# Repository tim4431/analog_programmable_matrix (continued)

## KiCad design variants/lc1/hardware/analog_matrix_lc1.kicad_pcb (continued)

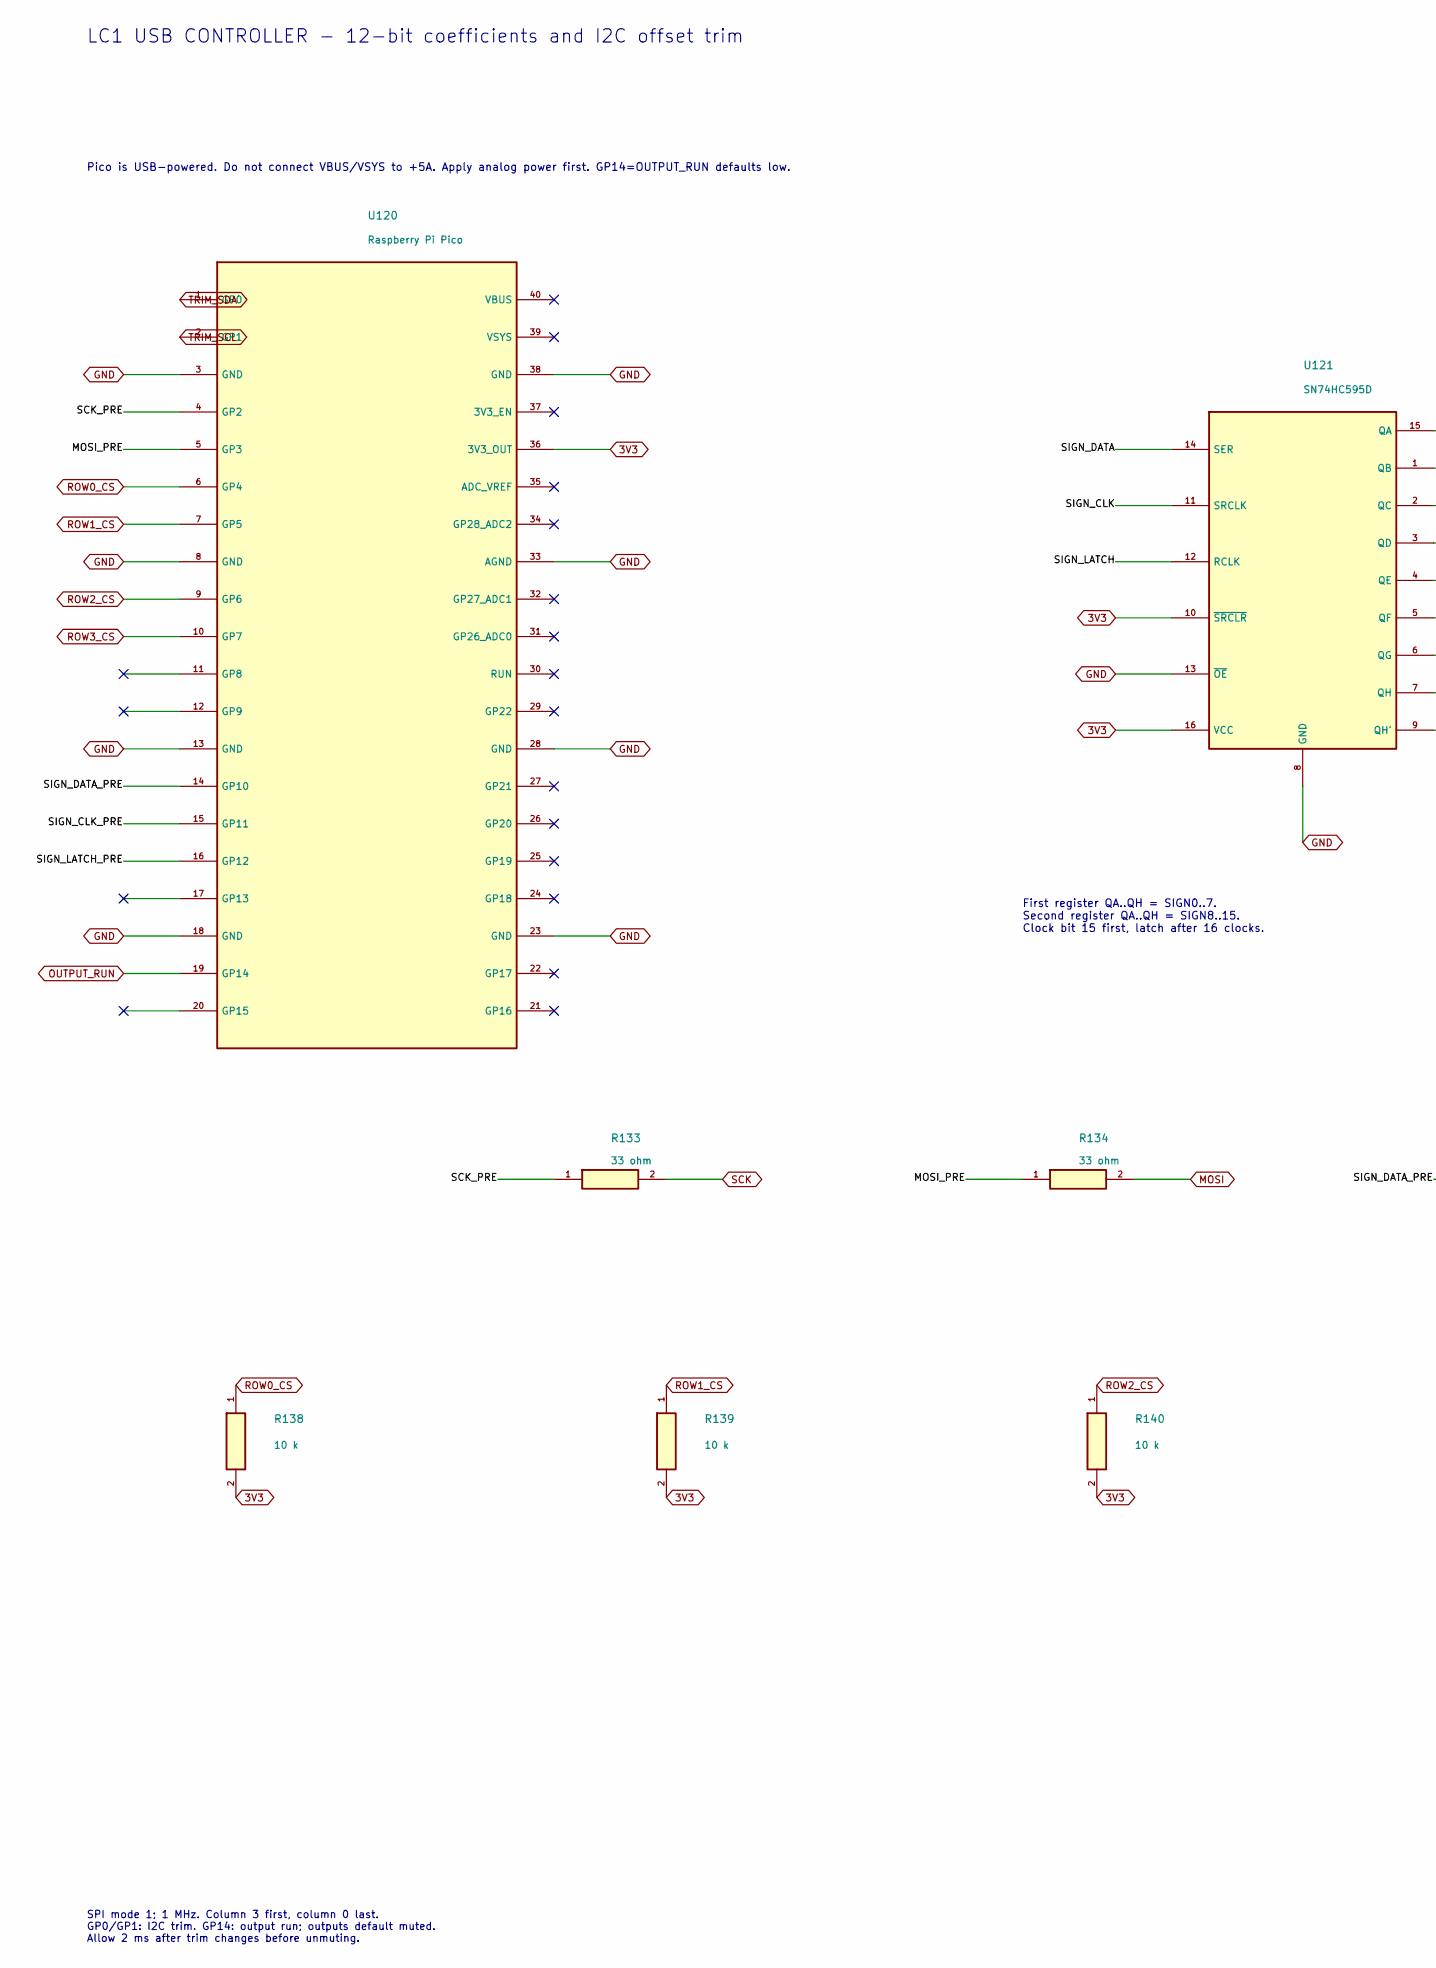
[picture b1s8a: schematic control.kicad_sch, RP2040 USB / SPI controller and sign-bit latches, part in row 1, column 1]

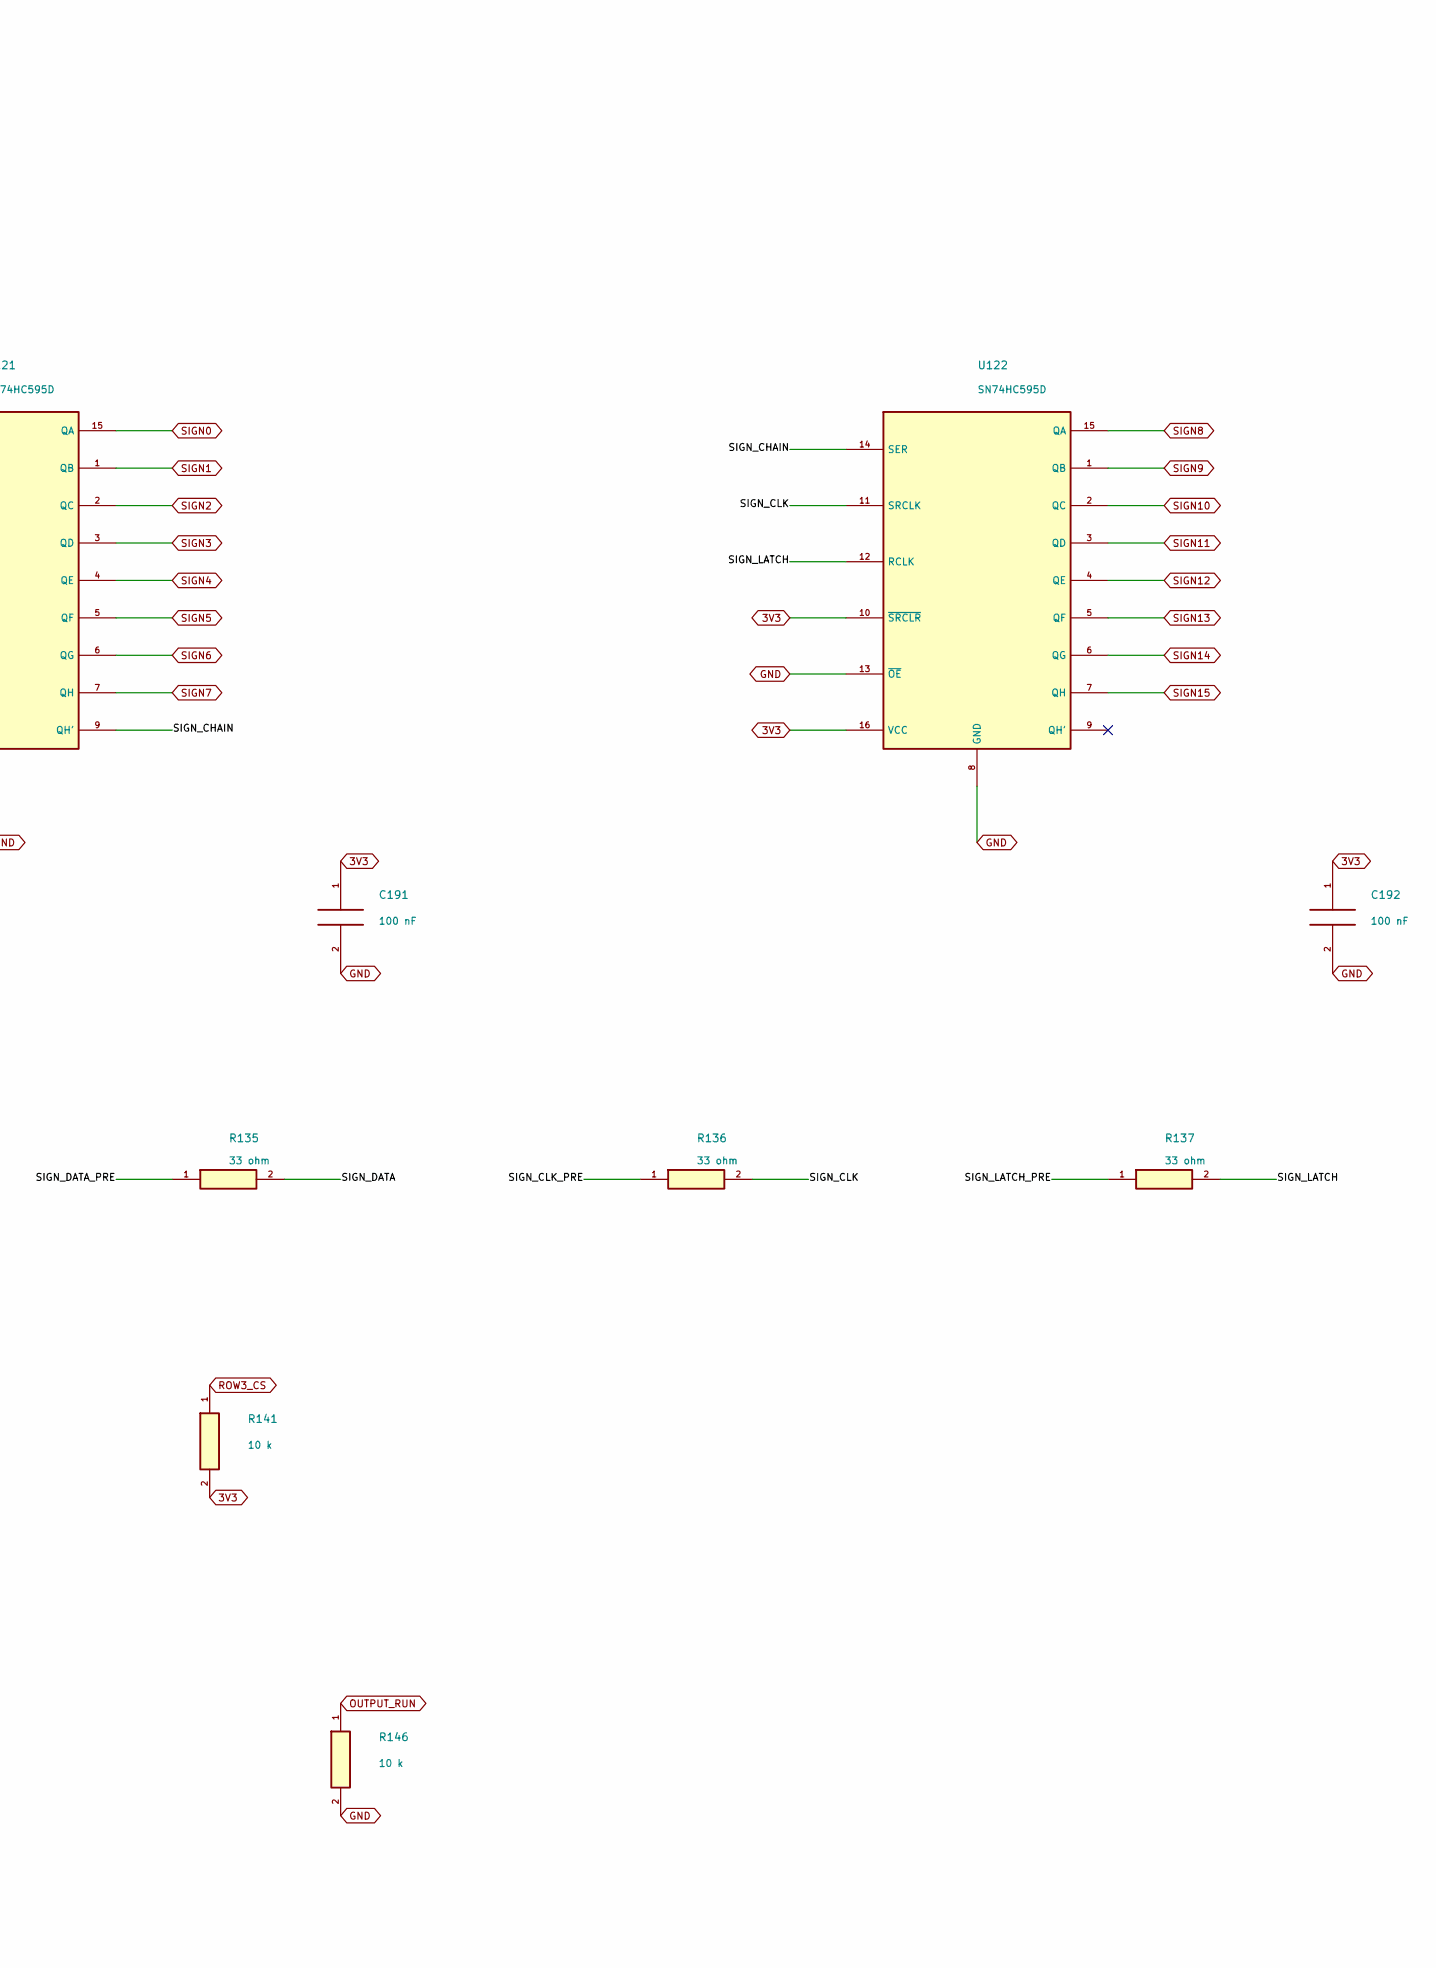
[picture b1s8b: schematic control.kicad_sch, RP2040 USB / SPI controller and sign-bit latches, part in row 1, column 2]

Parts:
C191, C192: 100 nF; C_0603_1608Metric; Rating 25V X7R minimum; effective C after bias
R133, R134, R135, R136, R137: 33 ohm; R_0603_1608Metric; Rating 0.1%, <=25ppm/C; 0.1W minimum
R138, R139, R140, R141, R146: 10 k; R_0603_1608Metric; Rating 0.1%, <=25ppm/C; 0.1W minimum
U120: Raspberry Pi Pico; Pico_2x20_Socket_17.78mm
U121, U122: SN74HC595D; SOIC-16_3.9x9.9mm_P1.27mm

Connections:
3V3: C191.1, C192.1, R138.2, R139.2, R140.2, R141.2, U120.36 (3V3_OUT), U121.10 (~SRCLR), U121.16 (VCC), U122.10 (~SRCLR), U122.16 (VCC); also elsewhere on the board
/Control/MOSI_PRE: R134.1, U120.5 (GP3)
/Control/SCK_PRE: R133.1, U120.4 (GP2)
/Control/SIGN_CHAIN: U121.9 (QH'), U122.14 (SER)
/Control/SIGN_CLK: R136.2, U121.11 (SRCLK), U122.11 (SRCLK)
/Control/SIGN_CLK_PRE: R136.1, U120.15 (GP11)
/Control/SIGN_DATA: R135.2, U121.14 (SER)
/Control/SIGN_DATA_PRE: R135.1, U120.14 (GP10)
/Control/SIGN_LATCH: R137.2, U121.12 (RCLK), U122.12 (RCLK)
/Control/SIGN_LATCH_PRE: R137.1, U120.16 (GP12)
GND: C191.2, C192.2, R146.2, U120.3 (GND), U120.8 (GND), U120.13 (GND), U120.18 (GND), U120.23 (GND), U120.28 (GND), U120.33 (AGND), U120.38 (GND), U121.8 (GND), U121.13 (~OE), U122.8 (GND), U122.13 (~OE); also elsewhere on the board
MOSI: R134.2; also elsewhere on the board
OUTPUT_RUN: R146.1, U120.19 (GP14); also elsewhere on the board
ROW0_CS: R138.1, U120.6 (GP4); also elsewhere on the board
ROW1_CS: R139.1, U120.7 (GP5); also elsewhere on the board
ROW2_CS: R140.1, U120.9 (GP6); also elsewhere on the board
ROW3_CS: R141.1, U120.10 (GP7); also elsewhere on the board
SCK: R133.2; also elsewhere on the board
SIGN0: U121.15 (QA); also elsewhere on the board
SIGN1: U121.1 (QB); also elsewhere on the board
SIGN2: U121.2 (QC); also elsewhere on the board
SIGN3: U121.3 (QD); also elsewhere on the board
SIGN4: U121.4 (QE); also elsewhere on the board
SIGN5: U121.5 (QF); also elsewhere on the board
SIGN6: U121.6 (QG); also elsewhere on the board
SIGN7: U121.7 (QH); also elsewhere on the board
SIGN8: U122.15 (QA); also elsewhere on the board
SIGN9: U122.1 (QB); also elsewhere on the board
SIGN10: U122.2 (QC); also elsewhere on the board
SIGN11: U122.3 (QD); also elsewhere on the board
SIGN12: U122.4 (QE); also elsewhere on the board
SIGN13: U122.5 (QF); also elsewhere on the board
SIGN14: U122.6 (QG); also elsewhere on the board
SIGN15: U122.7 (QH); also elsewhere on the board
TRIM_SCL: U120.2 (GP1); also elsewhere on the board
TRIM_SDA: U120.1 (GP0); also elsewhere on the board

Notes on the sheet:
LC1 USB CONTROLLER - 12-bit coefficients and I2C offset trim
Pico is USB-powered. Do not connect VBUS/VSYS to +5A. Apply analog power first. GP14=OUTPUT_RUN defaults low.
First register QA..QH = SIGN0..7. Second register QA..QH = SIGN8..15. Clock bit 15 first, latch after 16 clocks.
SPI mode 1; 1 MHz. Column 3 first, column 0 last. GP0/GP1: I2C trim. GP14: output run; outputs default muted. Allow 2 ms after trim changes before unmuting.

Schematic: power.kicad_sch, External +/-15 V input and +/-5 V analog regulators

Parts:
C193, C197: 47 uF / 35 V; C_Radial_D5.0mm_H11.0mm_P2.00mm; Rating 35V polarized
C194: 330 nF; C_0603_1608Metric; Rating 25V X7R minimum; effective C after bias
C195, C199: 10 uF / 16 V; C_Radial_D5.0mm_H11.0mm_P2.00mm; Rating 16V polarized
C196, C200: 100 nF; C_0603_1608Metric; Rating 25V X7R minimum; effective C after bias
C198: 2.2 uF; CP_EIA-3216-18_Kemet-A; Rating 35V polarized
D1, D2: 1N4002; D_DO-41_SOD81_P10.16mm_Horizontal
J9: 3-pin terminal; TerminalBlock_Phoenix_MKDS-1,5-3-5.08_1x03_P5.08mm_Horizont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
U130: L7805CV; TO-220-3_Vertical
U131: L7905CV; TO-220-3_Vertical

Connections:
+5A: C195.1, C196.1, D1.2 (A), U130.3 (OUT); also elsewhere on the board
+15V: C193.1, C194.1, D1.1 (K), J9.1 (+15V), U130.1 (IN); also elsewhere on the board
-5A: C199.2, C200.1, D2.1 (K), U131.3 (OUT); also elsewhere on the board
-15V: C197.2, C198.2, D2.2 (A), J9.3 (-15V), U131.2 (IN); also elsewhere on the board
GND: C193.2, C194.2, C195.2, C196.2, C197.1, C198.1, C199.1, C200.2, J9.2 (GND), U130.2 (GND), U131.1 (GND); also elsewhere on the board

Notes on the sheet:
External +/-15 V input and +/-5 V analog regulators
External regulated +/-15 V, at least 1 A per rail. Regulator heatsinks <=15 C/W. Negative regulator tab is -15 V; positive regulator tab is GND.
Observe all polarized capacitor signs. Use the shown electrolytic/tantalum regulator capacitors; do not substitute ceramic-only outputs. Regulator dissipation is roughly 3 W per device; verify temperature under sustained DC output loads. +/-5A supplies the analog core.

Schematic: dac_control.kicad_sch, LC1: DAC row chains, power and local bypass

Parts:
C300, C301, C302, C303, C304, C305, C306, C307, C308, C309, C310, C311, C312, C313, C314, C315: 100 nF; C_0603_1608Metric; Rating 25V X7R
U300, U301, U302, U303, U304, U305, U306, U307, U308, U309, U310, U311, U312, U313, U314, U315: DAC7811IDGSR; VSSOP-10_3x3mm_P0.5mm

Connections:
+5A: C300.1, C301.1, C302.1, C303.1, C304.1, C305.1, C306.1, C307.1, C308.1, C309.1, C310.1, C311.1, C312.1, C313.1, C314.1, C315.1, U300.8 (VDD), U301.8 (VDD), U302.8 (VDD), U303.8 (VDD), U304.8 (VDD), U305.8 (VDD), U306.8 (VDD), U307.8 (VDD), U308.8 (VDD), U309.8 (VDD), U310.8 (VDD), U311.8 (VDD), U312.8 (VDD), U313.8 (VDD), U314.8 (VDD), U315.8 (VDD); also elsewhere on the board
DAC_CHAIN_0_0: U300.7 (SDO), U301.5 (SDIN)
DAC_CHAIN_0_1: U301.7 (SDO), U302.5 (SDIN)
DAC_CHAIN_0_2: U302.7 (SDO), U303.5 (SDIN)
DAC_CHAIN_1_0: U304.7 (SDO), U305.5 (SDIN)
DAC_CHAIN_1_1: U305.7 (SDO), U306.5 (SDIN)
DAC_CHAIN_1_2: U306.7 (SDO), U307.5 (SDIN)
DAC_CHAIN_2_0: U308.7 (SDO), U309.5 (SDIN)
DAC_CHAIN_2_1: U309.7 (SDO), U310.5 (SDIN)
DAC_CHAIN_2_2: U310.7 (SDO), U311.5 (SDIN)
DAC_CHAIN_3_0: U312.7 (SDO), U313.5 (SDIN)
DAC_CHAIN_3_1: U313.7 (SDO), U314.5 (SDIN)
DAC_CHAIN_3_2: U314.7 (SDO), U315.5 (SDIN)
GND: C300.2, C301.2, C302.2, C303.2, C304.2, C305.2, C306.2, C307.2, C308.2, C309.2, C310.2, C311.2, C312.2, C313.2, C314.2, C315.2, U300.3 (GND), U301.3 (GND), U302.3 (GND), U303.3 (GND), U304.3 (GND), U305.3 (GND), U306.3 (GND), U307.3 (GND), U308.3 (GND), U309.3 (GND), U310.3 (GND), U311.3 (GND), U312.3 (GND), U313.3 (GND), U314.3 (GND), U315.3 (GND); also elsewhere on the board
MOSI: U300.5 (SDIN), U304.5 (SDIN), U308.5 (SDIN), U312.5 (SDIN); also elsewhere on the board
ROW0_CS: U300.6 (SYNC), U301.6 (SYNC), U302.6 (SYNC), U303.6 (SYNC); also elsewhere on the board
ROW1_CS: U304.6 (SYNC), U305.6 (SYNC), U306.6 (SYNC), U307.6 (SYNC); also elsewhere on the board
ROW2_CS: U308.6 (SYNC), U309.6 (SYNC), U310.6 (SYNC), U311.6 (SYNC); also elsewhere on the board
ROW3_CS: U312.6 (SYNC), U313.6 (SYNC), U314.6 (SYNC), U315.6 (SYNC); also elsewhere on the board
SCK: U300.4 (SCLK), U301.4 (SCLK), U302.4 (SCLK), U303.4 (SCLK), U304.4 (SCLK), U305.4 (SCLK), U306.4 (SCLK), U307.4 (SCLK), U308.4 (SCLK), U309.4 (SCLK), U310.4 (SCLK), U311.4 (SCLK), U312.4 (SCLK), U313.4 (SCLK), U314.4 (SCLK), U315.4 (SCLK); also elsewhere on the board

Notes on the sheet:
DAC7811 - FOUR INDEPENDENT ROW CHAINS
5 V DAC supplies; 3.3 V SPI inputs meet VIH. SDO is 5 V: connect only to the next DAC. SPI mode 1, 1 MHz. Send column 3 first, column 0 last; each SYNC rising edge updates its row. Each 100 nF bypass must sit at its DAC supply pins. Analog units are on their output-row sheets.
ROW 0 / COLUMN 0
ROW 0 / COLUMN 1
ROW 0 / COLUMN 2
ROW 0 / COLUMN 3
ROW 1 / COLUMN 0
ROW 1 / COLUMN 1
ROW 1 / COLUMN 2
ROW 1 / COLUMN 3
ROW 2 / COLUMN 0
ROW 2 / COLUMN 1
ROW 2 / COLUMN 2
ROW 2 / COLUMN 3
ROW 3 / COLUMN 0
ROW 3 / COLUMN 1
ROW 3 / COLUMN 2
ROW 3 / COLUMN 3

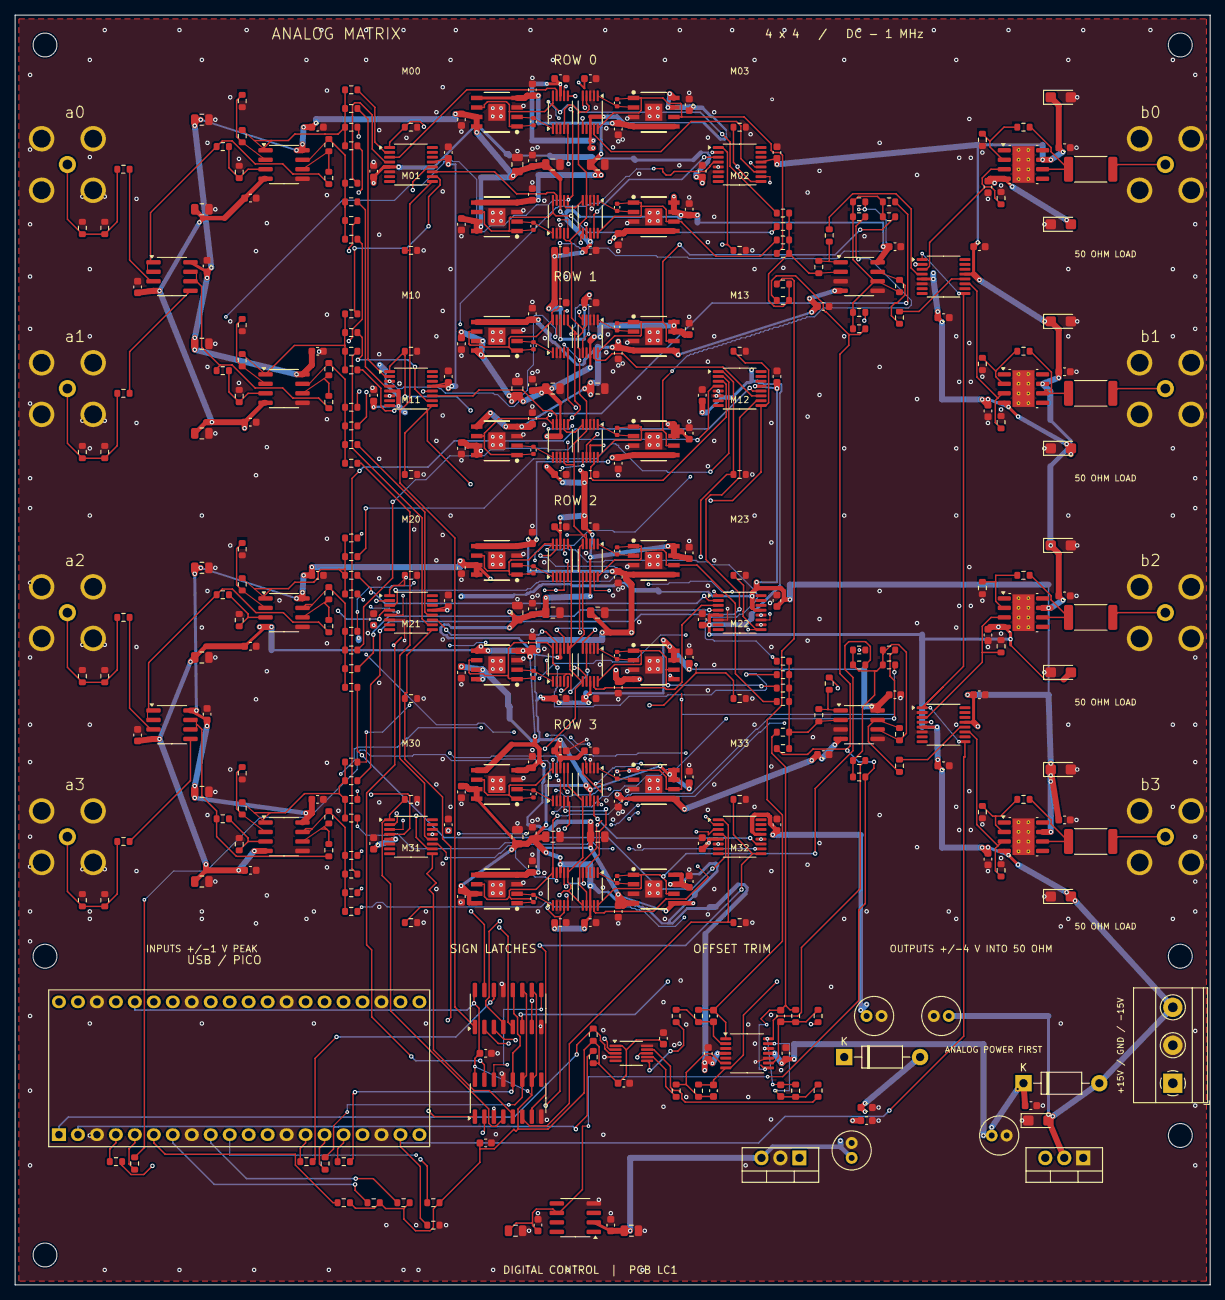
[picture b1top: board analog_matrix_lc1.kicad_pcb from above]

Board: 4 copper layers, 160.0 x 170.0 mm, 393 parts (0 on the bottom side), 205 nets.

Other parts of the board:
H1, H2, H3, H4, H5, H6: MountingHole_3.2mm_M3

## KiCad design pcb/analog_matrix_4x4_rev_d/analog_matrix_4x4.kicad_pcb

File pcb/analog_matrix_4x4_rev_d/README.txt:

REVISION D / MECHANICAL M3 - COMPACT LAYOUT
PCB shrinks from Rev C 180 x 210 to 160 x 170 mm (28.04% less area).
The M3 enclosure is 180 x 192 x 60 mm (25.52% less footprint than M2).
Eight vertical 50-ohm BNCs retain 30 mm row pitch. Power entry faces outward
at the right edge. Heatsink envelopes remain 35 x 13 x 38.1 mm.
The 36 protected inverting-node copper shapes are rigidly translated intact;
other routing and component placements change. Circuit values, MCU and
firmware are unchanged. No PCB parasitic extraction has been performed.
Use Rev D manufacturing files with M3 mechanics; earlier designs were removed
from the first public release. Confirm temperature and connector fit on a prototype.
compaction.json gives exact component and protected-node translations.
revision_validation.json compares electrical nets and local shapes to Rev C.

4x4 programmable analog matrix - PCB D / electrical A2
2026-10-01

OPEN AND EDIT
Extract the complete package. Open analog_matrix_4x4.kicad_pro in KiCad
8.0.6 or newer, then open the PCB or its root schematic.
Keep the local symbol and footprint libraries beside the project.

There are nine sheets: index, all inputs, four complete output rows,
offset trim, control and power. Each output row now has a continuous
left-to-right signal path. Power units and decouplers stay near the
corresponding signal circuits. The project has 428 components and 18
distinct footprint types. schematic.pdf is exported from this source.
The PCB is 160 x 170 mm, with four copper layers and six M3 holes. All
components are on the front. Four repeated analog rows run from input
conditioning at the left, through the DAC/TIA cells, to 50-ohm output
drivers at the right. Pico control, DC trim and power sit below the rows.
No potentiometers or manual-mode jumpers are included in this revision.

PCB FILES
analog_matrix_4x4.kicad_pcb is the editable board. Read
FABRICATION_AND_BRINGUP.txt for stackup, assembly, cooling and first tests.
pcb_front.svg, pcb_back.svg and assembly_front.svg are physical previews.
assembly_bom.csv includes ratings and DNP flags; placement_front.csv gives
positions in mm. Select actual passive MPNs before an assembly order.
fabrication/ contains Gerbers and separate PTH/NPTH drill files.
drc.json is the native PCB-check report; pcb_audit.json compares every
electrical pad/net assignment with the checked schematic.
Rerun checks after edits. DRC does not establish measured analog performance.
The A2 SPICE results below are circuit-level results, not PCB extraction.

A2 CHANGES
- Consolidated the earlier 16-sheet schematic into nine readable sheets.
- Changed all 32 RBRP/RBRN branch resistors from 49.9 ohms to 150 ohms.
  Feedback-input loop tests found only about 33 degrees phase margin in
  the original loaded positive buffer. Final polarity-buffer estimates
  are approximately 61-66 degrees. R_OUT and RMUTE remain 49.9 ohms.
- Corrected AD5544BRSZ to SSOP-28, 5.3 x 10.2 mm body, 0.65 mm pitch.
  The A1 TSSOP assignment was wrong. Pad-number checks alone missed it.
- Coax labels now explicitly identify BNC 031-5329-52RFX connectors.
- Pico GPIO mapping is unchanged. Firmware estimated full-code gain is
  now 1.021, reflecting the 150-ohm branches. It is NOT measured calibration.
  Re-measure calibration after the resistor change; an existing Pico
  calibration.json overrides the factory estimates at startup.

CIRCUIT SCOPE
Four high-impedance inputs, +/-1 V peak each, DC through 1 MHz target.
Four outputs, up to +/-4 V peak at an EXTERNAL 50-ohm termination.
The on-board 49.9-ohm series resistor is the source termination. A high-
impedance receiver sees approximately twice the specified loaded voltage.
Coefficients range from -1 to +1. The MCU programs static coefficients;
it does not sample or synthesize the signal waveform.

Nominal final SPICE: about 0.758% amplitude reduction at 1 MHz after DC
normalization, approximately 7.24 MHz sampled -3 dB frequency, 3.971 V peak
from the full-scale matched-row surrogate, and 119 ns 1% step settling
with a 50-ohm / 20p load. Read the included SPICE report and MODEL_SCOPE.txt
before interpreting those figures. The AD5544 model is approximate, full-
matrix trim is idealized, and transient switches use a static reduction.

The report does NOT establish 1% relative accuracy at every coefficient.
An illustrative feedthrough model gives roughly 14.6% amplitude error at
M=0.01 and 0.00573 V/V residual for M=0 at 1 MHz. Absolute coefficient error
and relative coefficient error are different specifications. The 1 nF
load step stalled numerically and remains unresolved. Phase matching,
PCB parasitics, thermal behavior and hardware calibration remain unproven.

POWER AND CONTROL
Use external regulated +/-15 V and USB power for the original Raspberry Pi
Pico. +5A and -5A are +/-5 V analog rail names, not current ratings. Apply
analog supplies before powering the Pico; there is no automatic supply
supervisor. Firmware starts muted. L7805/L7905 heat dissipation and heat-
sinking must be checked as part of PCB/mechanical work.

AD5544 sets coefficient magnitude; TMUX6219 selects polarity. Shared LDAC
updates the four row DACs; two 74HC595 devices latch sixteen sign bits.
The fifth AD5544 controls four DC trim voltages. Refer to firmware/CONTROL.txt
for USB JSON commands, pin mapping, both-sign calibration and persistence.

FOOTPRINT AND PART NOTES
- ADA4899 ordering code is ADA4899-1YRDZ. Its custom RD-8-1 footprint has
  a 2.29 x 2.29 mm exposed paddle mapped to schematic pad 9, connected to GND.
- THS3091DDAR uses the DDA PowerPAD footprint with ground pad and thermal
  vias. Keep its 1.21k feedback resistor and do not fit a feedback capacitor.
- Pico footprint is for the original Pico with two 20-pin rows 17.78 mm
  apart; verify sockets or headers before ordering.
- Coax footprint is Amphenol 031-5329-52RFX vertical 50-ohm BNC. Reassign the footprint
  before substituting another connector geometry.
- Polarized capacitors use pad 1 positive and pad 2 negative, including
  those on negative rails. Rating fields specify voltage/power needs.
  Select actual purchasable parts that fit; this is not a procurement BOM.
- L7905 tab is -15 V; L7805 tab is GND. Account for heatsink insulation.
- OriginalRef fields and reference_map.json preserve the descriptive
  identifiers used by the simulation and prior design.

VALIDATION
Native KiCad parsing, ERC, PDF/netlist export and footprint SVG parsing
passed. ERC has zero violations; all 428 components match the intended
pin/net sets; all assigned symbol pins match footprint pads. Reports are
erc.json, connectivity_audit.json, footprint_audit.json and package_audit.json.
All nine schematic pages were visually inspected.

Repeat from this project directory:
kicad-cli sch erc --format json --severity-all --exit-code-violations --output erc.json analog_matrix_4x4.kicad_sch
kicad-cli sch export netlist --format kicadxml --output validation_netlist.xml analog_matrix_4x4.kicad_sch
python tools/audit_kicad.py .
python tools/audit_footprints.py .
kicad-cli sch export pdf --output schematic.pdf analog_matrix_4x4.kicad_sch

Audits are snapshots; rerun them after editing. design_instances.json is
the intended part/pin list and must reflect deliberate circuit changes.
ERC does not prove analog stability or accuracy. The simulation package
contains editable .cir files, complete successful traces and model sources.

LIBRARIES AND LICENSES
Project library tables use ${KIPRJMOD}. Standard footprints are copied from
KiCad 8.0.6; see KiCad-footprints-LICENSE.txt and footprint_provenance.json.
3D models optionally use the installed KiCad library and are not required
to inspect copper/pad geometry. Vendor SPICE models retain their original
copyright/disclaimer notices; they are not represented as open-source code.

PRIMARY PACKAGE REFERENCES
https://www.analog.com/media/en/technical-documentation/data-sheets/AD5544_5554.pdf
https://www.analog.com/media/en/technical-documentation/data-sheets/ADA4899-1.pdf
https://www.ti.com/lit/ds/symlink/ths3091.pdf
https://www.ti.com/lit/ds/symlink/tmux6219.pdf
https://www.ti.com/lit/ds/symlink/opa810.pdf
https://datasheets.raspberrypi.com/pico/pico-datasheet.pdf

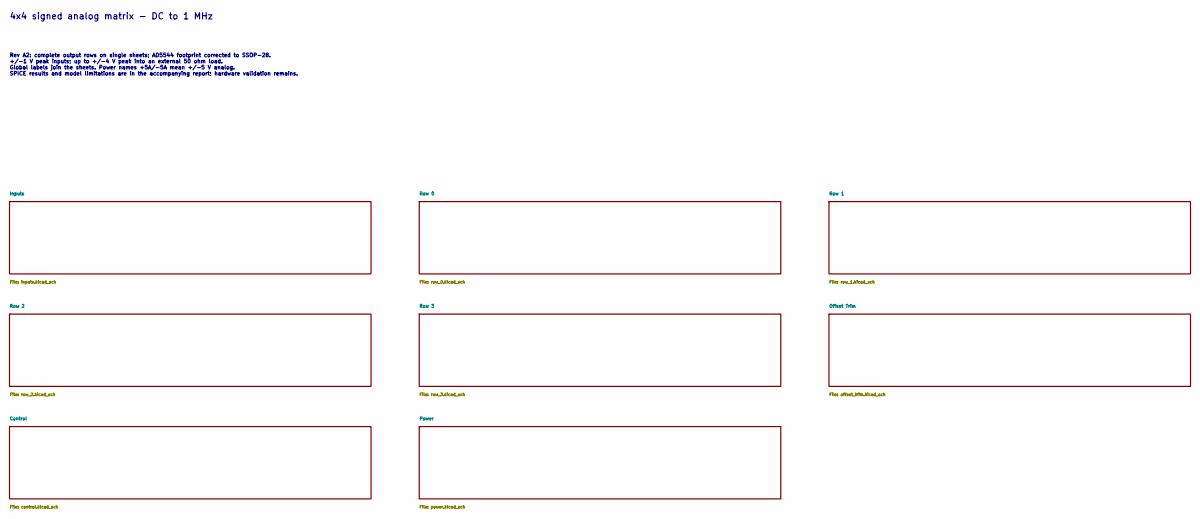
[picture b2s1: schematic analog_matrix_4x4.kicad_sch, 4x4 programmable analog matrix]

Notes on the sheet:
4x4 signed analog matrix - DC to 1 MHz
Rev A2: complete output rows on single sheets; AD5544 footprint corrected to SSOP-28. +/-1 V peak inputs; up to +/-4 V peak into an external 50 ohm load. Global labels join the sheets. Power names +5A/-5A mean +/-5 V analog. SPICE results and model limitations are in the accompanying report; hardwa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
